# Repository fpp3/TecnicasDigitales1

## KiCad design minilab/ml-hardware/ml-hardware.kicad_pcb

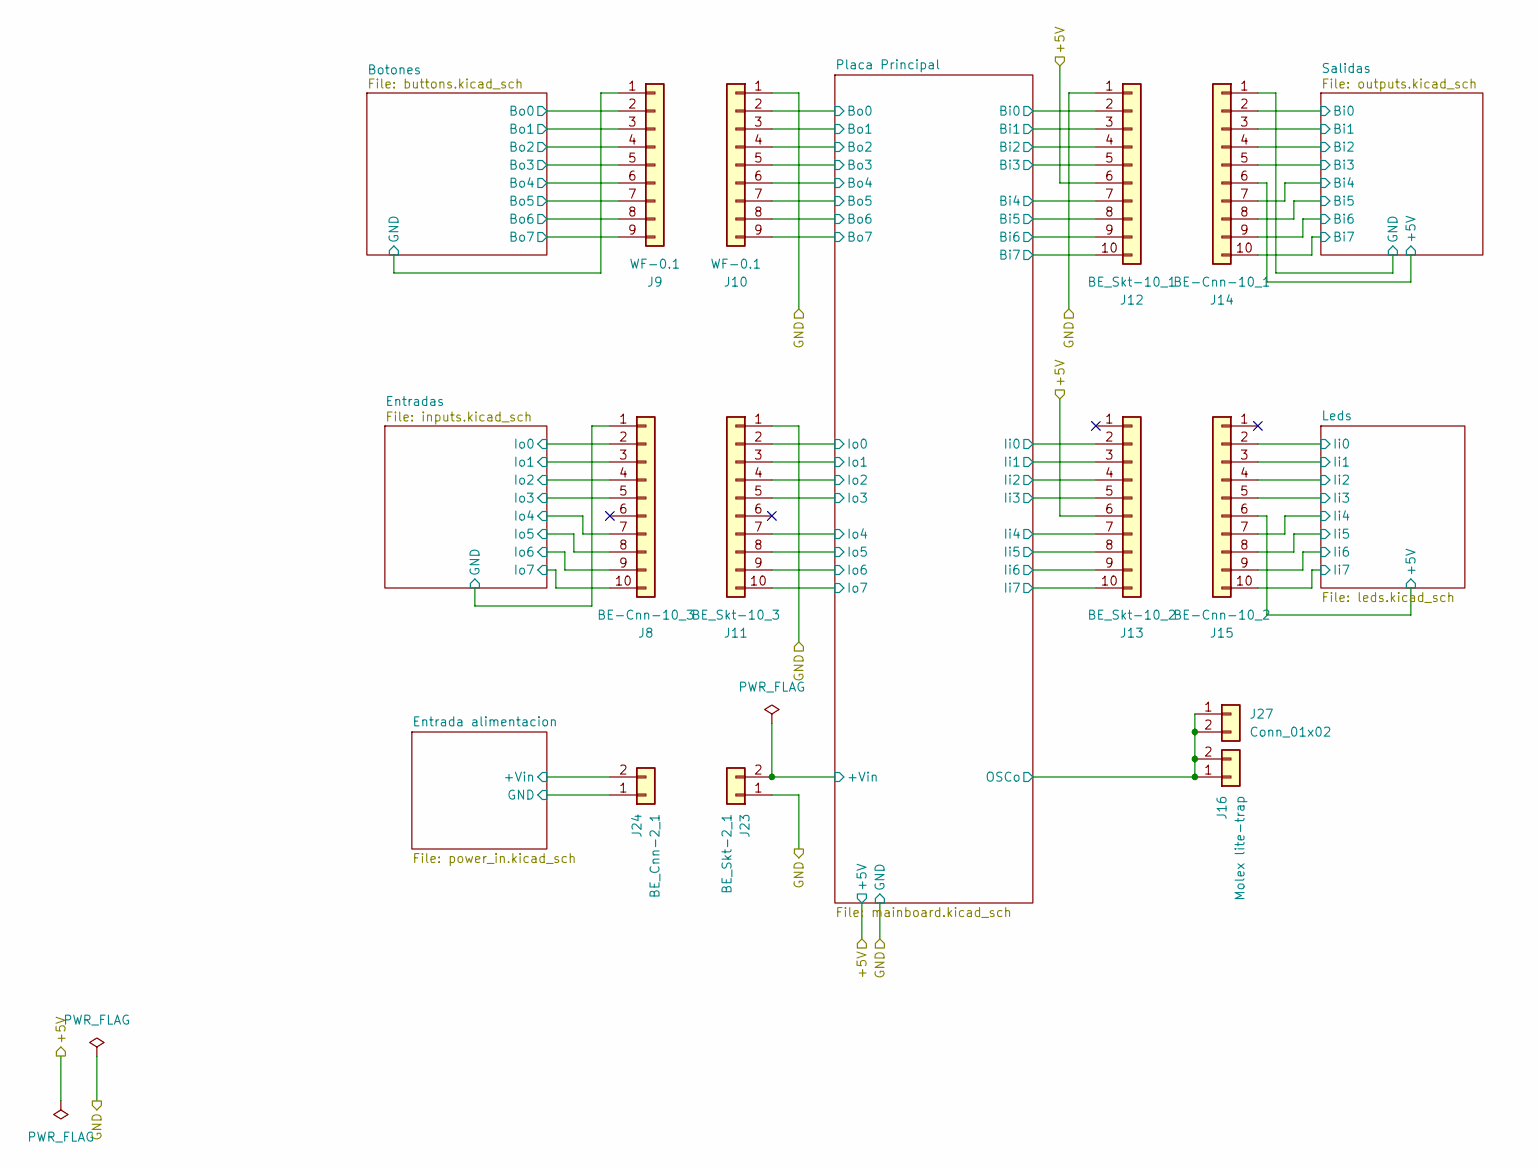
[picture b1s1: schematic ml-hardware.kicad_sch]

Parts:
J8: BE-Cnn-10_3; EdgeConn-10
J9, J10: WF-0.1; Molex_KK-254_AE-6410-09A_1x09_P2.54mm_Vertical
J11: BE_Skt-10_3; EdgeSocket-10
J12: BE_Skt-10_1; EdgeSocket-10
J13: BE_Skt-10_2; EdgeSocket-10
J14: BE-Cnn-10_1; EdgeConn-10
J15: BE-Cnn-10_2; EdgeConn-10
J16: Molex lite-trap; Molex-Lite_trap
J23: BE_Skt-2_1; EdgeSocket-2
J24: BE_Cnn-2_1; EdgeConn-2
J27: Conn_01x02; PinSocket_1x02_P2.54mm_Horizontal

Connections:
/+5V: J12.6, J13.6; also elsewhere on the board
/Botones/Bo0: J9.2; also elsewhere on the board
/Botones/Bo1: J9.3; also elsewhere on the board
/Botones/Bo2: J9.4; also elsewhere on the board
/Botones/Bo3: J9.5; also elsewhere on the board
/Botones/Bo4: J9.6; also elsewhere on the board
/Botones/Bo5: J9.7; also elsewhere on the board
/Botones/Bo6: J9.8; also elsewhere on the board
/Botones/Bo7: J9.9; also elsewhere on the board
/Botones/GND: J9.1; also elsewhere on the board
/Entrada alimentacion/+Vin: J24.2; also elsewhere on the board
/Entrada alimentacion/GND: J24.1; also elsewhere on the board
/Entradas/GND: J8.1; also elsewhere on the board
/Entradas/I0: J8.2; also elsewhere on the board
/Entradas/I1: J8.3; also elsewhere on the board
/Entradas/I2: J8.4; also elsewhere on the board
/Entradas/I3: J8.5; also elsewhere on the board
/Entradas/I4: J8.7; also elsewhere on the board
/Entradas/I5: J8.8; also elsewhere on the board
/Entradas/I6: J8.9; also elsewhere on the board
/Entradas/I7: J8.10; also elsewhere on the board
/GND: J10.1, J11.1, J12.1, J23.1; also elsewhere on the board
/Leds/+5V: J15.6; also elsewhere on the board
/Leds/Ii0: J15.2; also elsewhere on the board
/Leds/Ii1: J15.3; also elsewhere on the board
/Leds/Ii2: J15.4; also elsewhere on the board
/Leds/Ii3: J15.5; also elsewhere on the board
/Leds/Ii4: J15.7; also elsewhere on the board
/Leds/Ii5: J15.8; also elsewhere on the board
/Leds/Ii6: J15.9; also elsewhere on the board
/Leds/Ii7: J15.10; also elsewhere on the board
/Placa Principal/+Vin: J23.2; also elsewhere on the board
/Placa Principal/Bi0: J10.2, J12.2
/Placa Principal/Bi1: J10.3, J12.3
/Placa Principal/Bi2: J10.4, J12.4
/Placa Principal/Bi3: J10.5, J12.5
/Placa Principal/Bi4: J10.6, J12.7
/Placa Principal/Bi5: J10.7, J12.8
/Placa Principal/Bi6: J10.8, J12.9
/Placa Principal/Bi7: J10.9, J12.10
/Placa Principal/Ii0: J13.2; also elsewhere on the board
/Placa Principal/Ii1: J13.3; also elsewhere on the board
/Placa Principal/Ii2: J13.4; also elsewhere on the board
/Placa Principal/Ii3: J13.5; also elsewhere on the board
/Placa Principal/Ii4: J13.7; also elsewhere on the board
/Placa Principal/Ii5: J13.8; also elsewhere on the board
/Placa Principal/Ii6: J13.9; also elsewhere on the board
/Placa Principal/Ii7: J13.10; also elsewhere on the board
/Placa Principal/Io0: J11.2; also elsewhere on the board
/Placa Principal/Io1: J11.3; also elsewhere on the board
/Placa Principal/Io2: J11.4; also elsewhere on the board
/Placa Principal/Io3: J11.5; also elsewhere on the board
/Placa Principal/Io4: J11.7; also elsewhere on the board
/Placa Principal/Io5: J11.8; also elsewhere on the board
/Placa Principal/Io6: J11.9; also elsewhere on the board
/Placa Principal/Io7: J11.10; also elsewhere on the board
/Placa Principal/OSCo: J16.1, J16.2, J27.1, J27.2; also elsewhere on the board
/Salidas/+5V: J14.6; also elsewhere on the board
/Salidas/Bi0: J14.2; also elsewhere on the board
/Salidas/Bi1: J14.3; also elsewhere on the board
/Salidas/Bi2: J14.4; also elsewhere on the board
/Salidas/Bi3: J14.5; also elsewhere on the board
/Salidas/Bi4: J14.7; also elsewhere on the board
/Salidas/Bi5: J14.8; also elsewhere on the board
/Salidas/Bi6: J14.9; also elsewhere on the board
/Salidas/Bi7: J14.10; also elsewhere on the board
/Salidas/GND: J14.1; also elsewhere on the board

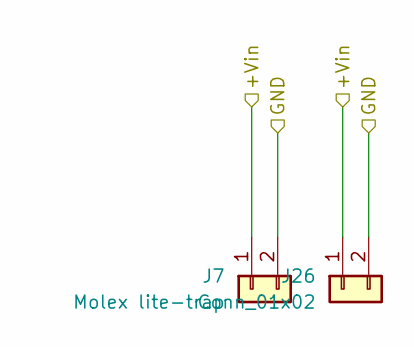
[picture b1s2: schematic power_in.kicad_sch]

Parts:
J7: Molex lite-trap; Molex-Lite_trap
J26: Conn_01x02; PinSocket_1x02_P2.54mm_Horizontal

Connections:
/Entrada alimentacion/+Vin: J7.1, J26.1; also elsewhere on the board
/Entrada alimentacion/GND: J7.2, J26.2; also elsewhere on the board

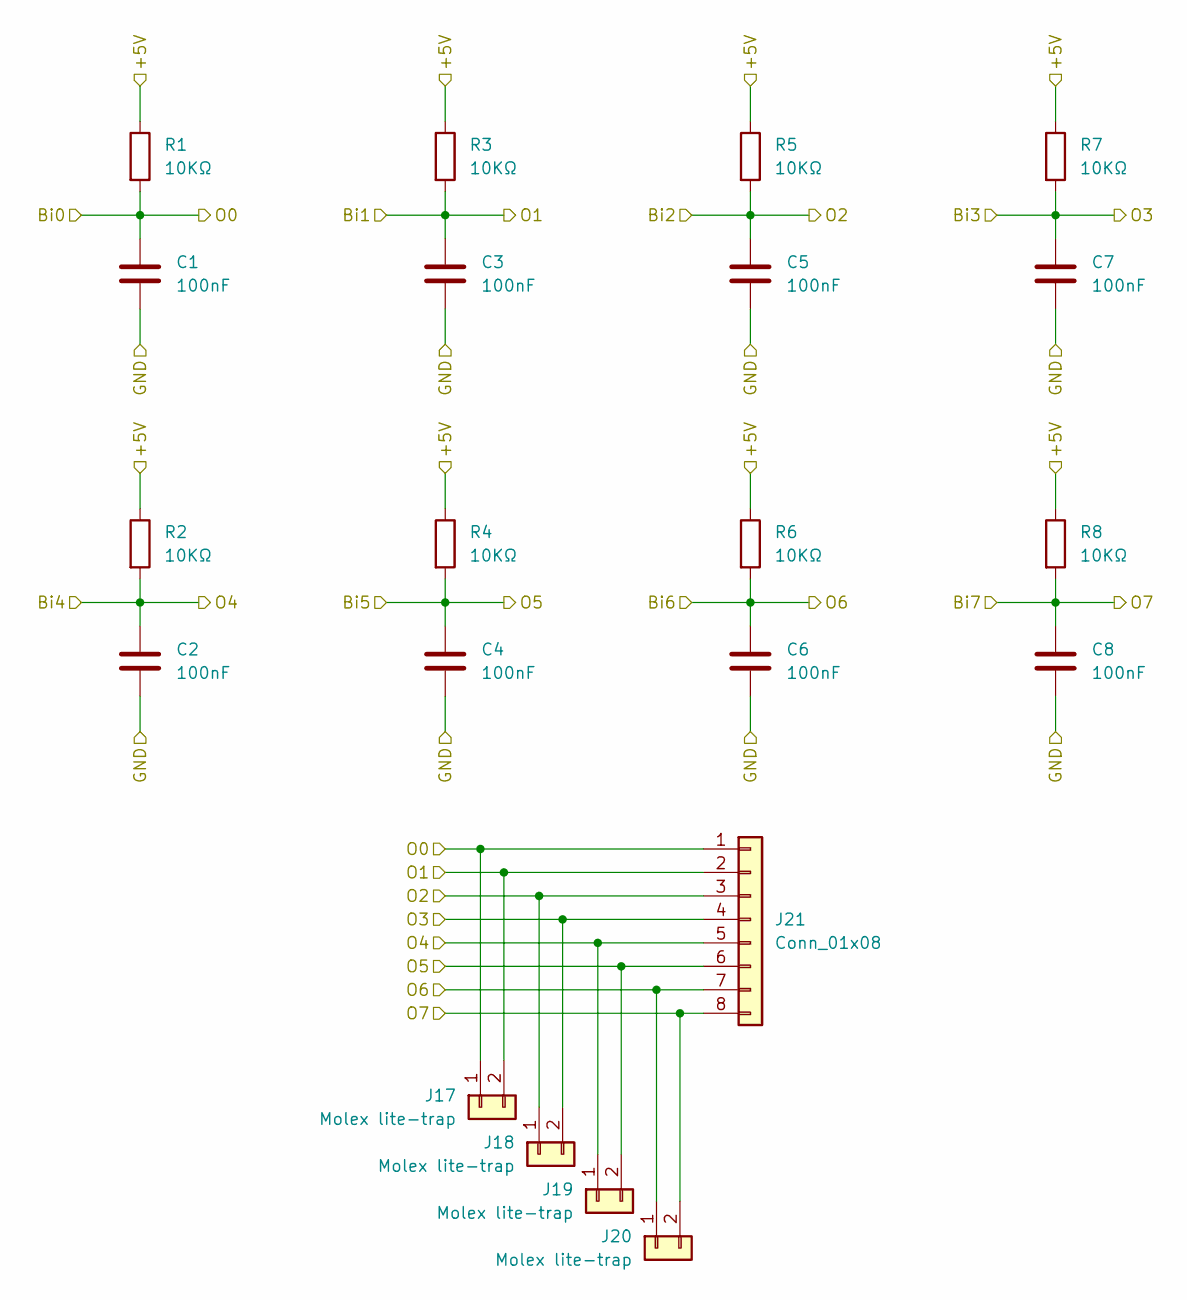
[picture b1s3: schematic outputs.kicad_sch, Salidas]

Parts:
C1, C2, C3, C4, C5, C6, C7, C8: 100nF; C_Disc_D6.0mm_W2.5mm_P5.00mm
J17, J18, J19, J20: Molex lite-trap; Molex-Lite_trap
J21: Conn_01x08; PinSocket_1x08_P2.54mm_Horizontal
R1, R2, R3, R4, R5, R6, R7, R8: 10KΩ; R_Axial_DIN0204_L3.6mm_D1.6mm_P5.08mm_Horizontal

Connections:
/Salidas/+5V: R1.1, R2.1, R3.1, R4.1, R5.1, R6.1, R7.1, R8.1; also elsewhere on the board
/Salidas/Bi0: C1.1, J17.1, J21.1, R1.2; also elsewhere on the board
/Salidas/Bi1: C3.1, J17.2, J21.2, R3.2; also elsewhere on the board
/Salidas/Bi2: C5.1, J18.1, J21.3, R5.2; also elsewhere on the board
/Salidas/Bi3: C7.1, J18.2, J21.4, R7.2; also elsewhere on the board
/Salidas/Bi4: C2.1, J19.1, J21.5, R2.2; also elsewhere on the board
/Salidas/Bi5: C4.1, J19.2, J21.6, R4.2; also elsewhere on the board
/Salidas/Bi6: C6.1, J20.1, J21.7, R6.2; also elsewhere on the board
/Salidas/Bi7: C8.1, J20.2, J21.8, R8.2; also elsewhere on the board
/Salidas/GND: C1.2, C2.2, C3.2, C4.2, C5.2, C6.2, C7.2, C8.2; also elsewhere on the board

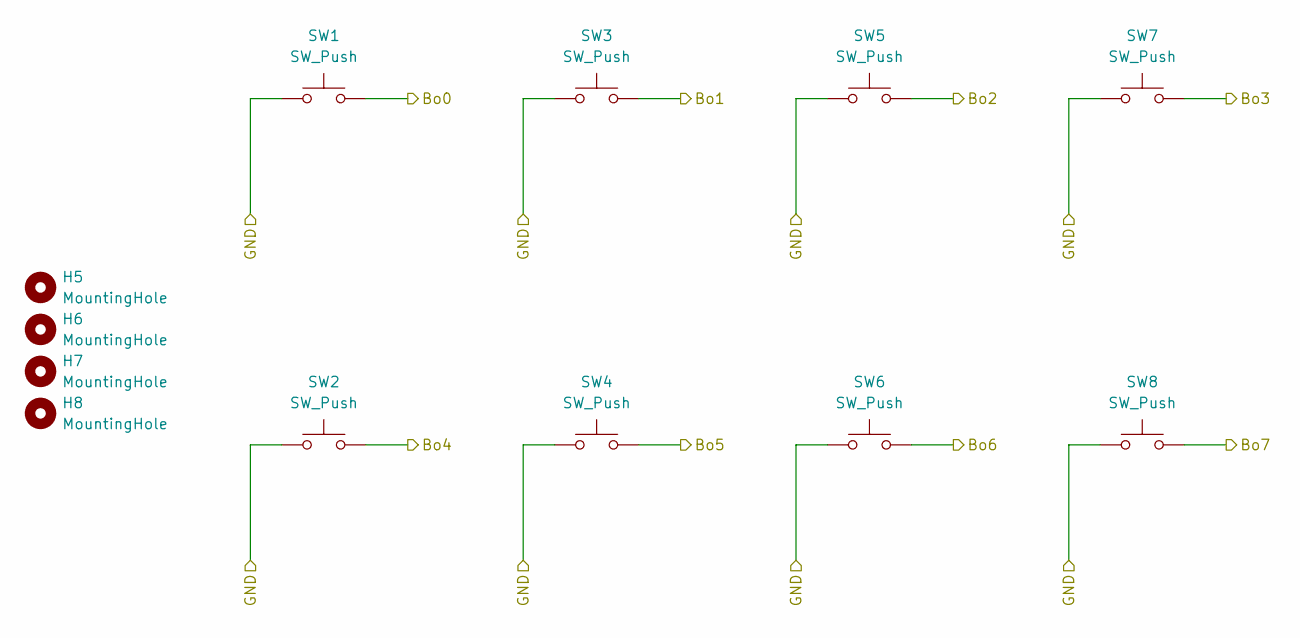
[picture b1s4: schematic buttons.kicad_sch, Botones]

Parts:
H5, H6, H7, H8: MountingHole; MountingHole_3.2mm_M3
SW1, SW2, SW3, SW4, SW5, SW6, SW7, SW8: SW_Push; SPDT_Switch

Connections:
/Botones/Bo0: SW1.2; also elsewhere on the board
/Botones/Bo1: SW3.2; also elsewhere on the board
/Botones/Bo2: SW5.2; also elsewhere on the board
/Botones/Bo3: SW7.2; also elsewhere on the board
/Botones/Bo4: SW2.2; also elsewhere on the board
/Botones/Bo5: SW4.2; also elsewhere on the board
/Botones/Bo6: SW6.2; also elsewhere on the board
/Botones/Bo7: SW8.2; also elsewhere on the board
/Botones/GND: SW1.1, SW2.1, SW3.1, SW4.1, SW5.1, SW6.1, SW7.1, SW8.1; also elsewhere on the board

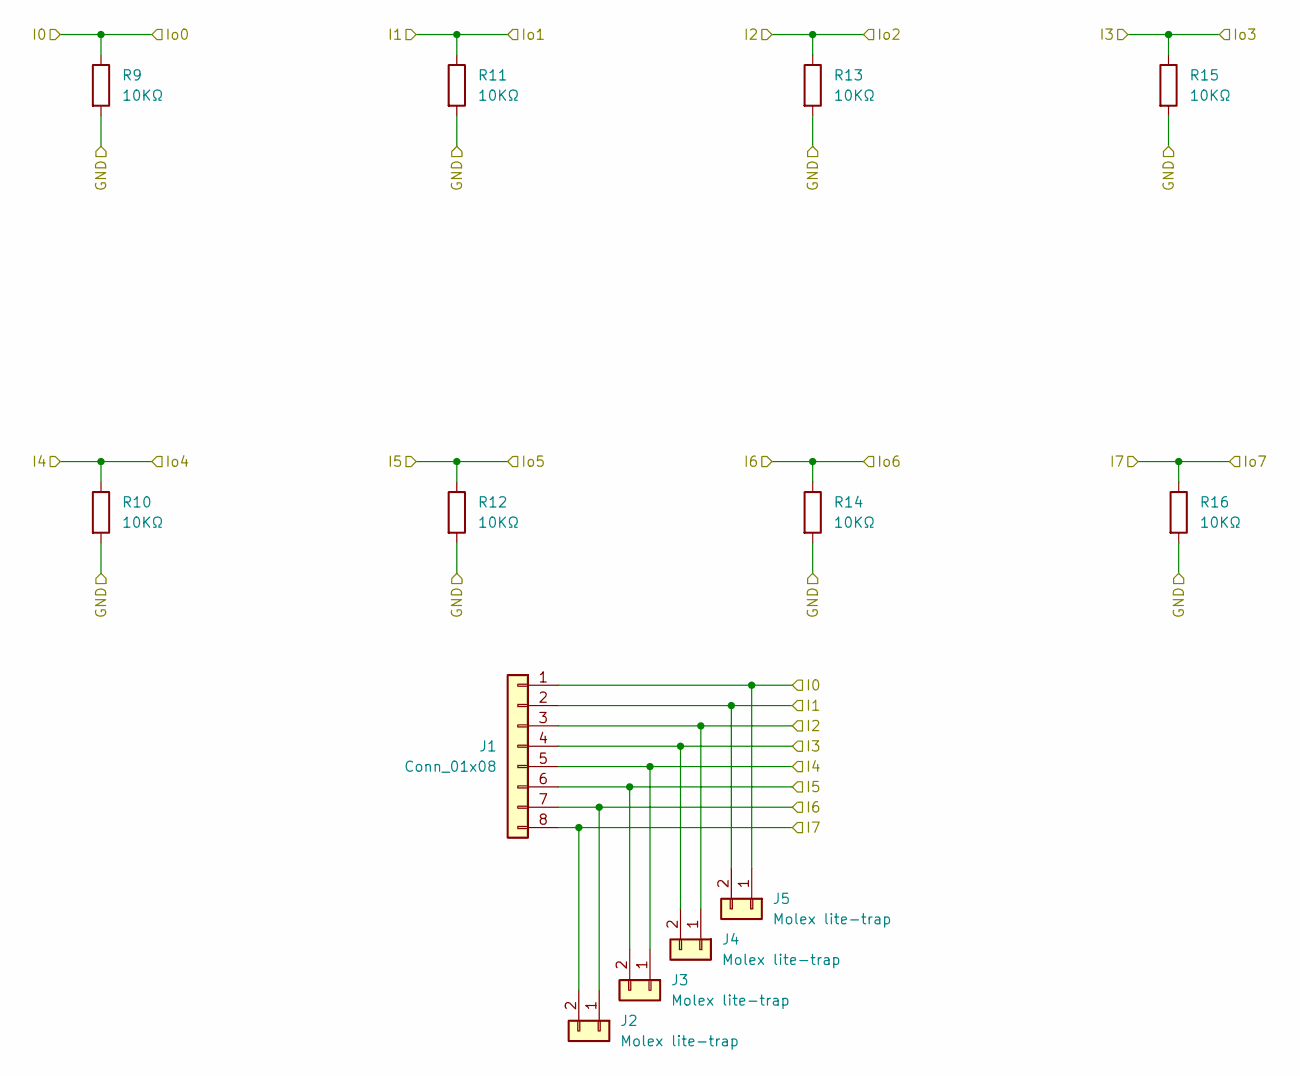
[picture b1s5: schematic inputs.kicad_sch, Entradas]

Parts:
J1: Conn_01x08; PinSocket_1x08_P2.54mm_Horizontal
J2, J3, J4, J5: Molex lite-trap; Molex-Lite_trap
R9, R10, R11, R12, R13, R14, R15, R16: 10KΩ; R_Axial_DIN0204_L3.6mm_D1.6mm_P5.08mm_Horizontal

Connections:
/Entradas/GND: R9.2, R10.2, R11.2, R12.2, R13.2, R14.2, R15.2, R16.2; also elsewhere on the board
/Entradas/I0: J1.1, J5.1, R9.1; also elsewhere on the board
/Entradas/I1: J1.2, J5.2, R11.1; also elsewhere on the board
/Entradas/I2: J1.3, J4.1, R13.1; also elsewhere on the board
/Entradas/I3: J1.4, J4.2, R15.1; also elsewhere on the board
/Entradas/I4: J1.5, J3.1, R10.1; also elsewhere on the board
/Entradas/I5: J1.6, J3.2, R12.1; also elsewhere on the board
/Entradas/I6: J1.7, J2.1, R14.1; also elsewhere on the board
/Entradas/I7: J1.8, J2.2, R16.1; also elsewhere on the board

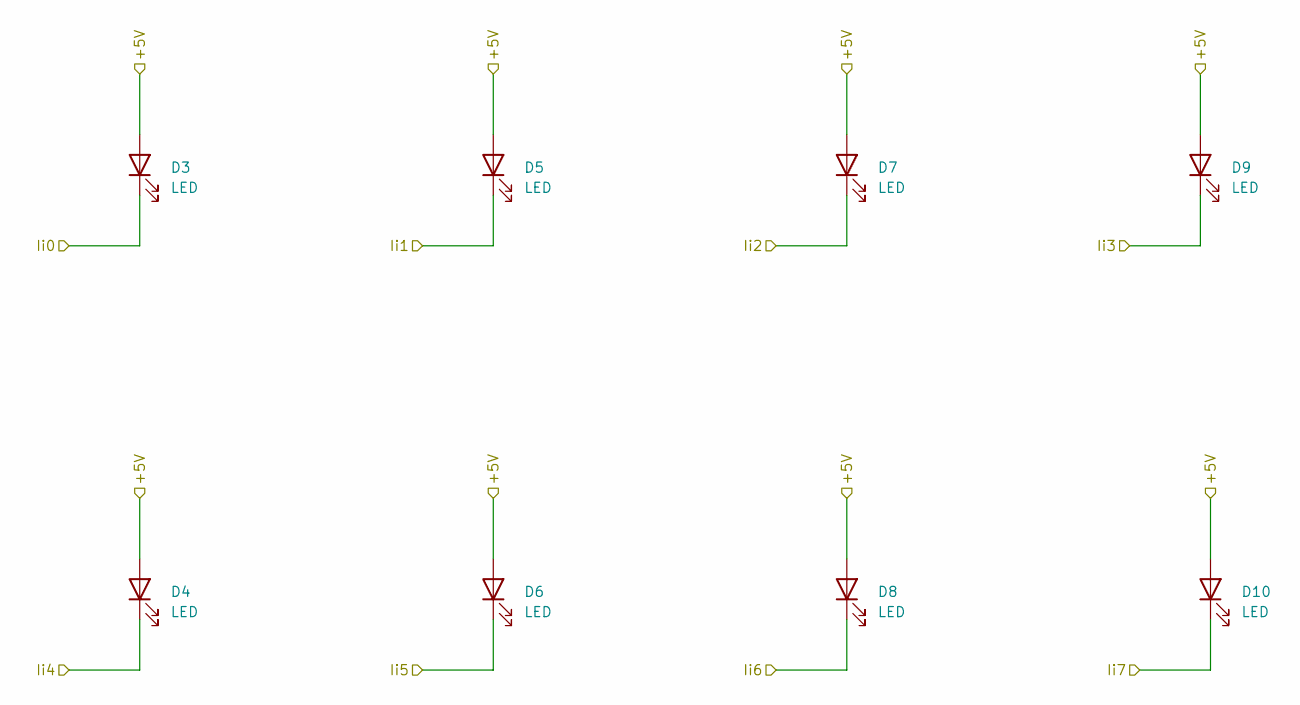
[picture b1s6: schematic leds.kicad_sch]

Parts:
D3, D4, D5, D6, D7, D8, D9, D10: LED; LED_Rectangular_W5.0mm_H2.0mm

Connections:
/Leds/+5V: D3.2 (A), D4.2 (A), D5.2 (A), D6.2 (A), D7.2 (A), D8.2 (A), D9.2 (A), D10.2 (A); also elsewhere on the board
/Leds/Ii0: D3.1 (K); also elsewhere on the board
/Leds/Ii1: D5.1 (K); also elsewhere on the board
/Leds/Ii2: D7.1 (K); also elsewhere on the board
/Leds/Ii3: D9.1 (K); also elsewhere on the board
/Leds/Ii4: D4.1 (K); also elsewhere on the board
/Leds/Ii5: D6.1 (K); also elsewhere on the board
/Leds/Ii6: D8.1 (K); also elsewhere on the board
/Leds/Ii7: D10.1 (K); also elsewhere on the board

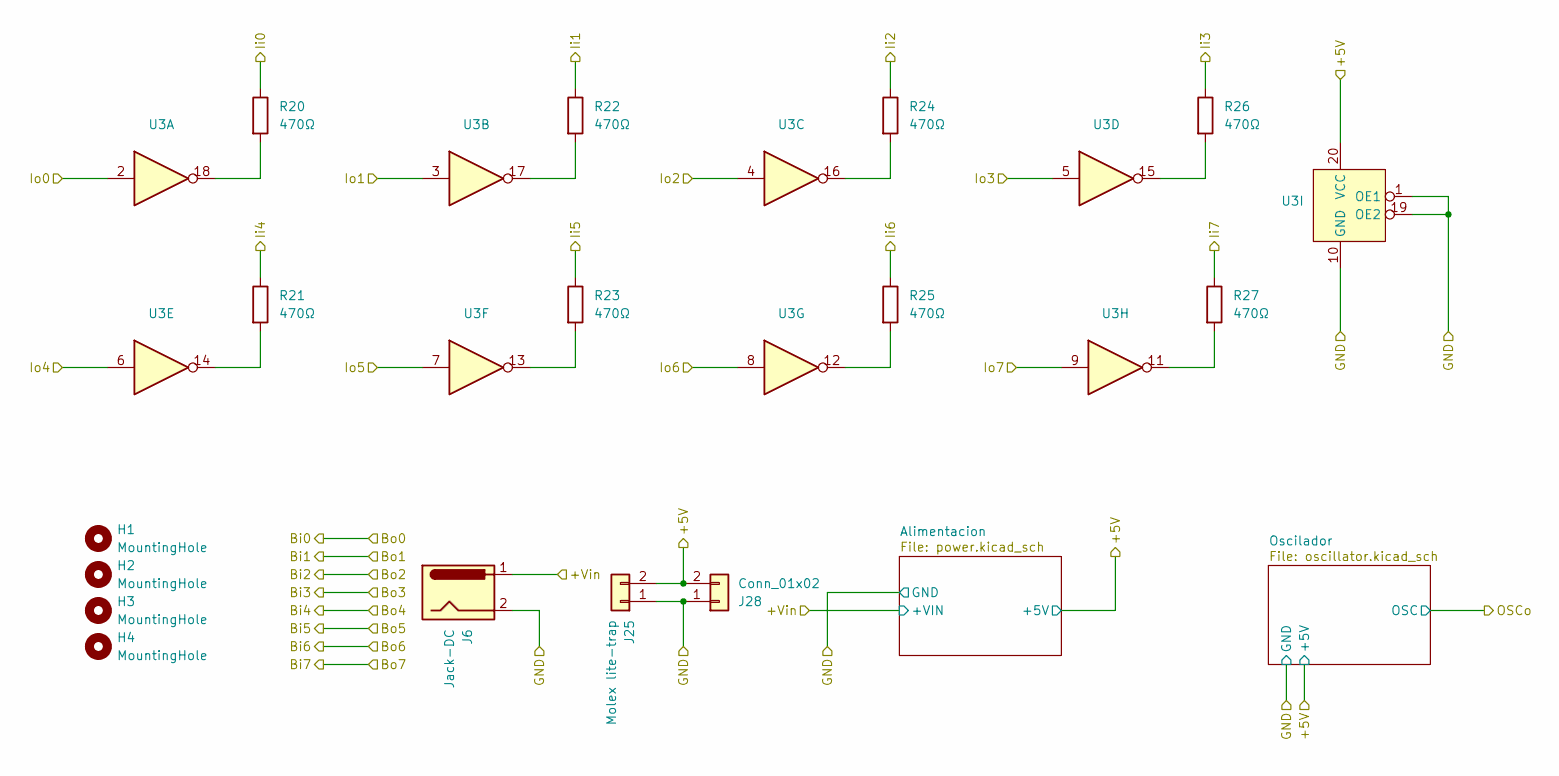
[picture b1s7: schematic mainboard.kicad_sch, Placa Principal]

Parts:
H1, H2, H3, H4: MountingHole; MountingHole_3.2mm_M3
J6: Jack-DC; BarrelJack_Horizontal
J25: Molex lite-trap; Molex-Lite_trap
J28: Conn_01x02; PinSocket_1x02_P2.54mm_Horizontal
R20, R27: 470Ω; R_Axial_DIN0204_L3.6mm_D1.6mm_P7.62mm_Horizontal
R21, R22, R23, R24, R25, R26: 470Ω; R_Axial_DIN0204_L3.6mm_D1.6mm_P5.08mm_Horizontal
U3: DIP-20_W7.62mm_LongPads

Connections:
/+5V: J25.2, J28.2, U3.20 (VCC); also elsewhere on the board
/GND: J6.2, J25.1, J28.1, U3.1 (OE1), U3.10 (GND), U3.19 (OE2); also elsewhere on the board
/Placa Principal/+Vin: J6.1; also elsewhere on the board
/Placa Principal/Ii0: R20.1; also elsewhere on the board
/Placa Principal/Ii1: R22.1; also elsewhere on the board
/Placa Principal/Ii2: R24.1; also elsewhere on the board
/Placa Principal/Ii3: R26.1; also elsewhere on the board
/Placa Principal/Ii4: R21.1; also elsewhere on the board
/Placa Principal/Ii5: R23.1; also elsewhere on the board
/Placa Principal/Ii6: R25.1; also elsewhere on the board
/Placa Principal/Ii7: R27.1; also elsewhere on the board
/Placa Principal/Io0: U3.2; also elsewhere on the board
/Placa Principal/Io1: U3.3; also elsewhere on the board
/Placa Principal/Io2: U3.4; also elsewhere on the board
/Placa Principal/Io3: U3.5; also elsewhere on the board
/Placa Principal/Io4: U3.6; also elsewhere on the board
/Placa Principal/Io5: U3.7; also elsewhere on the board
/Placa Principal/Io6: U3.8; also elsewhere on the board
/Placa Principal/Io7: U3.9; also elsewhere on the board
unnamed: R20.2, U3.18
unnamed: R21.2, U3.14
unnamed: R22.2, U3.17
unnamed: R23.2, U3.13
unnamed: R24.2, U3.16
unnamed: R25.2, U3.12
unnamed: R26.2, U3.15
unnamed: R27.2, U3.11

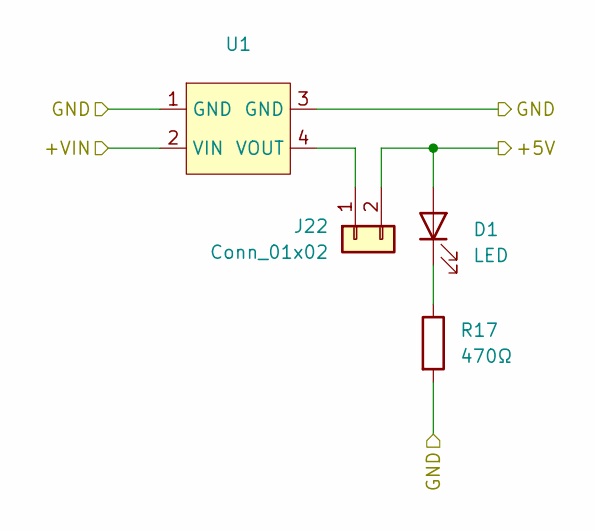
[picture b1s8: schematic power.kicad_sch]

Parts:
D1: LED; LED_Rectangular_W5.0mm_H2.0mm
J22: Conn_01x02; PinHeader_1x02_P2.54mm_Vertical
R17: 470Ω; R_Axial_DIN0204_L3.6mm_D1.6mm_P5.08mm_Horizontal
U1: DC-DC_buck

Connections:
/+5V: D1.2 (A), J22.2; also elsewhere on the board
/GND: R17.2, U1.1 (GND), U1.3 (GND); also elsewhere on the board
/Placa Principal/+Vin: U1.2 (VIN); also elsewhere on the board
unnamed: D1.1 (K), R17.1
unnamed: J22.1, U1.4 (VOUT)

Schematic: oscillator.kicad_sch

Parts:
C9: 470nF; C_Disc_D6.0mm_W2.5mm_P5.00mm
C10: 10nF; C_Disc_D6.0mm_W2.5mm_P5.00mm
D2: LED; LED_Rectangular_W5.0mm_H2.0mm
R18: 2K7Ω; R_Axial_DIN0204_L3.6mm_D1.6mm_P5.08mm_Horizontal
R19: 470Ω; R_Axial_DIN0204_L3.6mm_D1.6mm_P5.08mm_Horizontal
RV1: 1MΩ; Potentiometer_Bourns_3296W_Vertical
U2: NE555P; DIP-8_W7.62mm_LongPads

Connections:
/+5V: R18.1, U2.4 (R), U2.8 (VCC); also elsewhere on the board
/GND: C9.2, C10.2, R19.2, U2.1 (GND); also elsewhere on the board
/Placa Principal/OSCo: D2.2 (A), U2.3 (Q); also elsewhere on the board
unnamed: D2.1 (K), R19.1
unnamed: C10.1, U2.5 (CV)
unnamed: R18.2, RV1.1, RV1.2, U2.7 (DIS)
unnamed: C9.1, RV1.3, U2.2 (TR), U2.6 (THR)

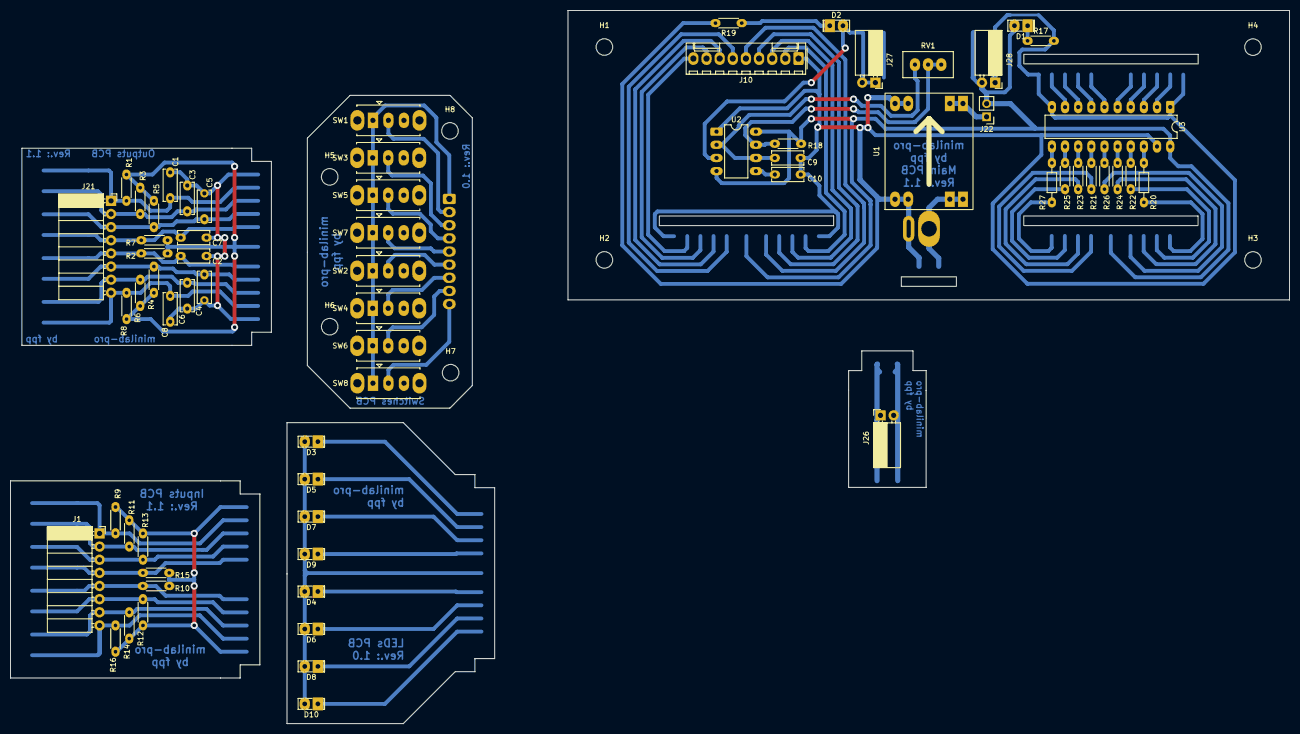
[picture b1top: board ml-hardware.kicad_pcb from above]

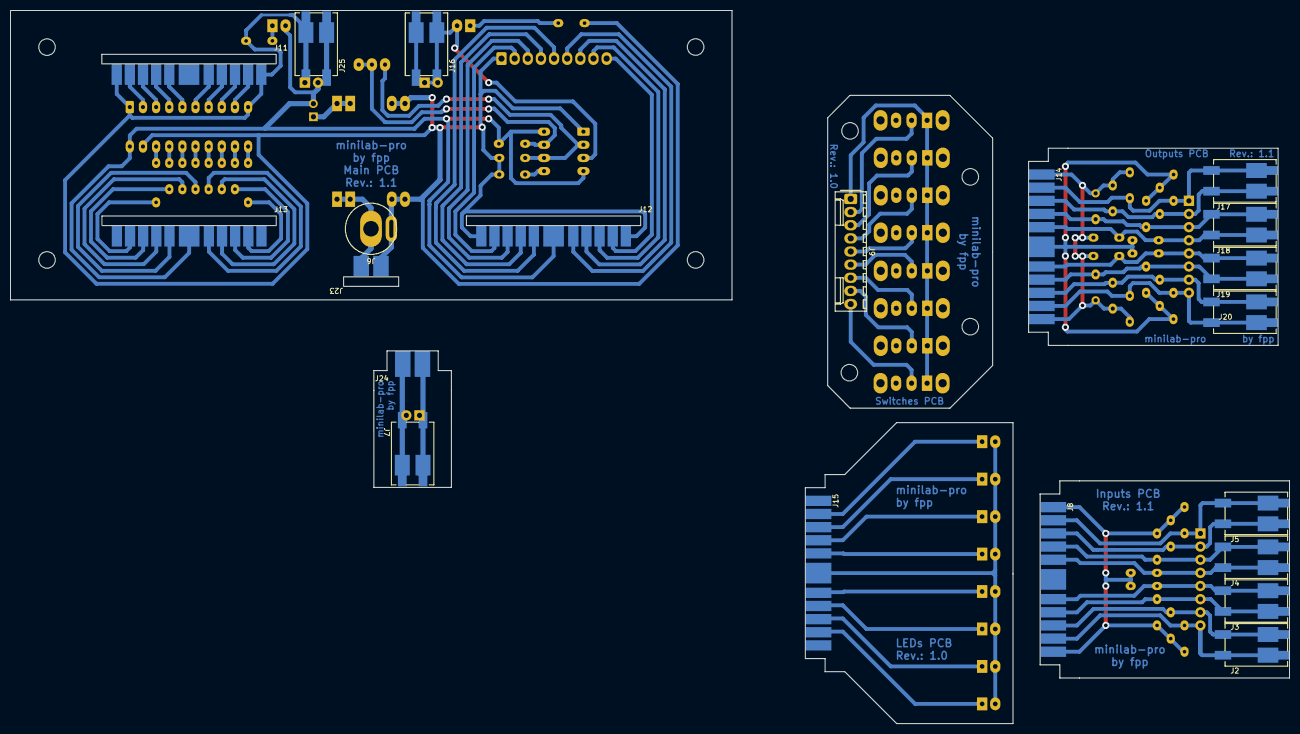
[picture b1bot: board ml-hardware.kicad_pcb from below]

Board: 2 copper layers, 247.2 x 137.8 mm, 95 parts (21 on the bottom side), 81 nets.

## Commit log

2025-04-15 minilab: Add base kicad project
2025-04-20 minilab: Add schematic, V1.0
2025-04-20 Add .gitignore entries for kicad projects
2025-04-25 minilab: change 4096 to 74HC540 for 1byte input
2025-04-26 minilab: Enforce "pcb/page" hierarchy on schematic
    This does not apply (necessarily) to subpages.
2025-04-30 minilab: Add PCB (wip)
2025-05-04 minilab: Added fp and sym lib tables
2025-06-01 TP1:creacion documento
2025-06-01 TP1: añadido paquete de karnaught y algunos mapas del ejercicio 1
2025-06-02 TP1:completado karnaught para ejercicio 1
2025-06-02 TP1: ejercicio uno casi terminado
2025-06-08 minilab: cambia jerarquia y agrega pcb
2025-06-08 tp1: Agrega capitulo 1
2025-06-09 TP1: ejercicio 1 finalizado
2025-06-09 minilab: Agrega 2da opc conectores y modelos 3d
2025-06-10 tp1: Agrega ejercicio 2
2025-06-10 tp1: Correcciones del ej1
2025-06-10 Dev minilab (#1)
    * minilab: Add PCB (wip)
    * minilab: Added fp and sym lib tables
    * minilab: cambia jerarquia y agrega pcb
    * minilab: Agrega 2da opc conectores y modelos 3d
2025-06-10 TP1: informe terminado (?
2025-06-10 TP1: ahora si
2025-06-10 tp1: Correcciones menores
2025-06-13 minilab: Corrige huella molex microfit y edge-*-02
2025-06-17 minilab: Actualiza placa de alimentacion
2025-08-11 Primera parte del minilab terminada
    Falta tapa frontal y revisar la ubicacion de la placa de leds en el step generado
2025-08-28 TP2: proyecto de xilinx con test bench
2025-08-31 Cleanup
2025-08-31 Borra todos los archivos de Xilinx y deja sources
2025-09-09 tp2: agrega tex y esquematico
2025-09-10 tp2: termina el informe
2025-09-11 ml-pro: Agrega C2 y embellecedor sw
2025-10-20 tp3: agrega codigo y anexos
